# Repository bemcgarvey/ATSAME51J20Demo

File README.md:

# ATSAME51J20Demo
 
## A demonstartion board for the ATSAME51J20 microcontroller.  Includes firmware projects to demonstrate many modules and features.  
  
### There is sample firmware for:
* Basic gpio and interrupts
* Event system
* DMA
* Full speed USB
* SD Card
* USB bootloader and file system boot loader (sd card)
* USB CDC device
* and more

### All firmware is built in MPLabX with MPLab Harmony 3 and the XC32 compiler.  
### Schematic and PCB were made with KiCAD

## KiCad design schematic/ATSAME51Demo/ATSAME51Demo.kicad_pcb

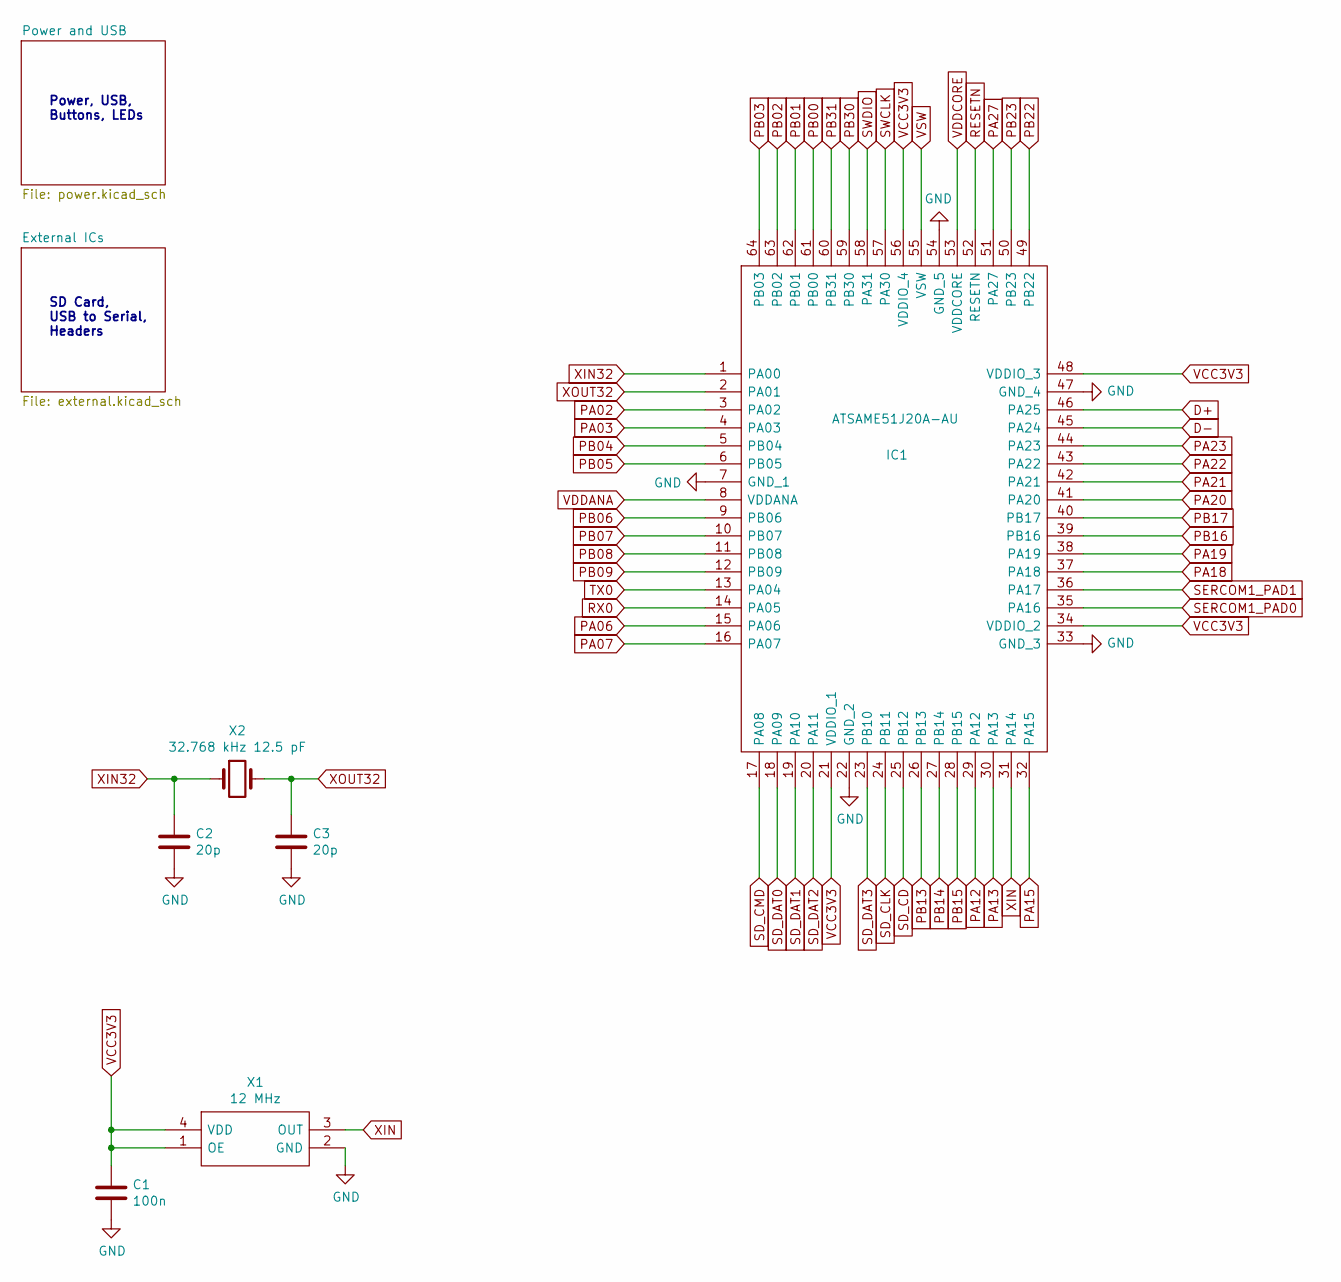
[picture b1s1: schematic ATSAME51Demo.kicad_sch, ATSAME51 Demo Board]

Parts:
C1: 100n; C_0402_1005Metric
C2, C3: 20p; C_0603_1608Metric
IC1: ATSAME51J20A-AU; QFP50P1200X1200X120-64N; Mouser Part Number 556-ATSAME51J20A-AU
X1: 12 MHz; ASTMUPCE3312000MHZLJET; Mouser Part Number 815-UPCE3312LJET
X2: 32.768 kHz 12.5 pF; CM9VT1A

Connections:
D+: IC1.46 (PA25); also elsewhere on the board
D-: IC1.45 (PA24); also elsewhere on the board
GND: C1.2, C2.2, C3.2, IC1.7 (GND_1), IC1.22 (GND_2), IC1.33 (GND_3), IC1.47 (GND_4), IC1.54 (GND_5), X1.2 (GND); also elsewhere on the board
PA02: IC1.3 (PA02); also elsewhere on the board
PA03: IC1.4 (PA03); also elsewhere on the board
PA06: IC1.15 (PA06); also elsewhere on the board
PA07: IC1.16 (PA07); also elsewhere on the board
PA12: IC1.29 (PA12); also elsewhere on the board
PA13: IC1.30 (PA13); also elsewhere on the board
PA15: IC1.32 (PA15); also elsewhere on the board
PA18: IC1.37 (PA18); also elsewhere on the board
PA19: IC1.38 (PA19); also elsewhere on the board
PA20: IC1.41 (PA20); also elsewhere on the board
PA21: IC1.42 (PA21); also elsewhere on the board
PA22: IC1.43 (PA22); also elsewhere on the board
PA23: IC1.44 (PA23); also elsewhere on the board
PA27: IC1.51 (PA27); also elsewhere on the board
PB00: IC1.61 (PB00); also elsewhere on the board
PB01: IC1.62 (PB01); also elsewhere on the board
PB02: IC1.63 (PB02); also elsewhere on the board
PB03: IC1.64 (PB03); also elsewhere on the board
PB04: IC1.5 (PB04); also elsewhere on the board
PB05: IC1.6 (PB05); also elsewhere on the board
PB06: IC1.9 (PB06); also elsewhere on the board
PB07: IC1.10 (PB07); also elsewhere on the board
PB08: IC1.11 (PB08); also elsewhere on the board
PB09: IC1.12 (PB09); also elsewhere on the board
PB13: IC1.26 (PB13); also elsewhere on the board
PB14: IC1.27 (PB14); also elsewhere on the board
PB15: IC1.28 (PB15); also elsewhere on the board
PB16: IC1.39 (PB16); also elsewhere on the board
PB17: IC1.40 (PB17); also elsewhere on the board
PB22: IC1.49 (PB22); also elsewhere on the board
PB23: IC1.50 (PB23); also elsewhere on the board
PB30: IC1.59 (PB30); also elsewhere on the board
PB31: IC1.60 (PB31); also elsewhere on the board
RESETN: IC1.52 (RESETN); also elsewhere on the board
RX0: IC1.14 (PA05); also elsewhere on the board
SD_CD: IC1.25 (PB12); also elsewhere on the board
SD_CLK: IC1.24 (PB11); also elsewhere on the board
SD_CMD: IC1.17 (PA08); also elsewhere on the board
SD_DAT0: IC1.18 (PA09); also elsewhere on the board
SD_DAT1: IC1.19 (PA10); also elsewhere on the board
SD_DAT2: IC1.20 (PA11); also elsewhere on the board
SD_DAT3: IC1.23 (PB10); also elsewhere on the board
SERCOM1_PAD0: IC1.35 (PA16); also elsewhere on the board
SERCOM1_PAD1: IC1.36 (PA17); also elsewhere on the board
SWCLK: IC1.57 (PA30); also elsewhere on the board
SWDIO: IC1.58 (PA31); also elsewhere on the board
TX0: IC1.13 (PA04); also elsewhere on the board
VCC3V3: C1.1, IC1.21 (VDDIO_1), IC1.34 (VDDIO_2), IC1.48 (VDDIO_3), IC1.56 (VDDIO_4), X1.1 (OE), X1.4 (VDD); also elsewhere on the board
VDDANA: IC1.8 (VDDANA); also elsewhere on the board
VDDCORE: IC1.53 (VDDCORE); also elsewhere on the board
VSW: IC1.55 (VSW); also elsewhere on the board
XIN: IC1.31 (PA14), X1.3 (OUT)
XIN32: C2.1, IC1.1 (PA00), X2.1
XOUT32: C3.1, IC1.2 (PA01), X2.2

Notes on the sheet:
Power, USB, Buttons, LEDs
SD Card, USB to Serial, Headers

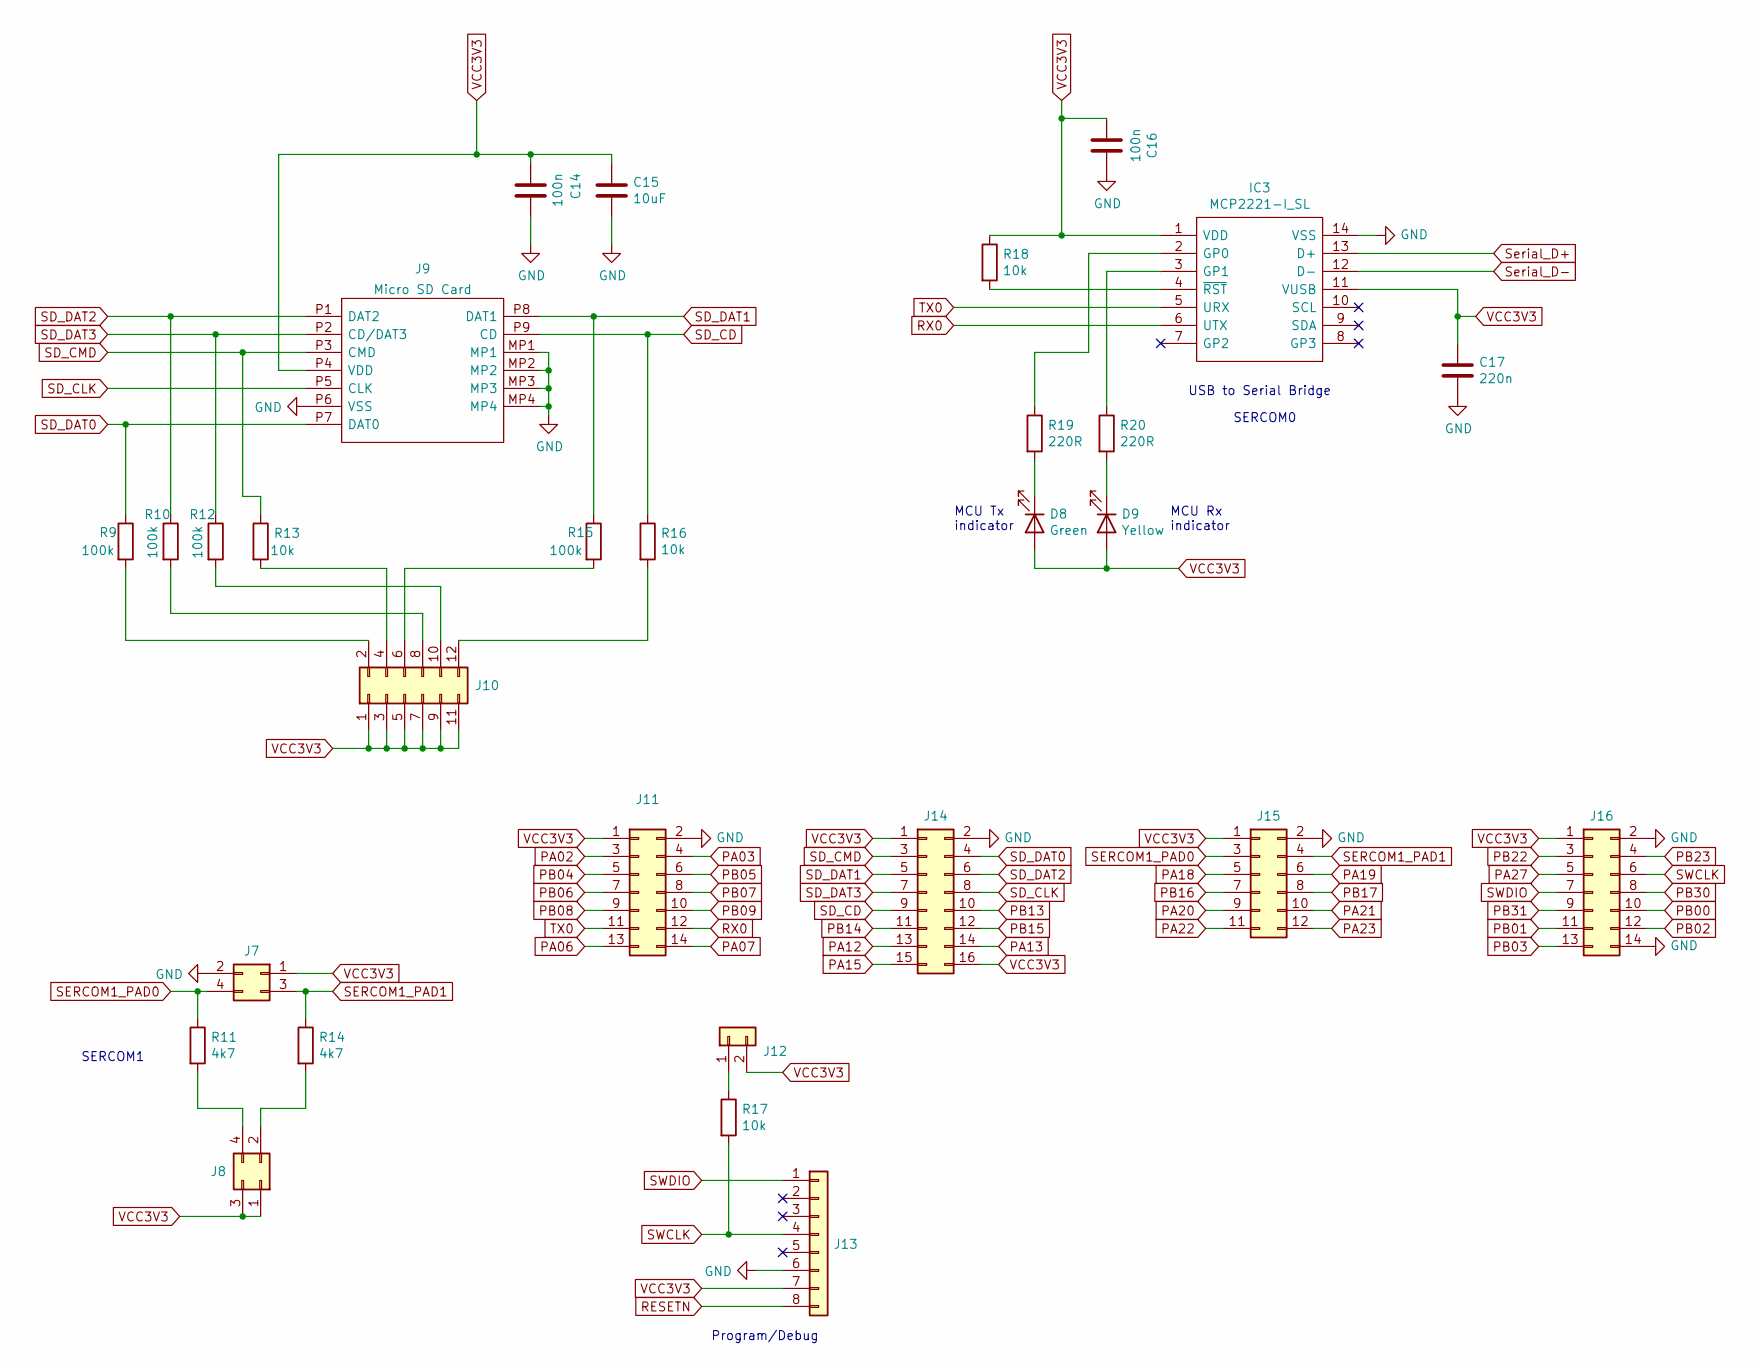
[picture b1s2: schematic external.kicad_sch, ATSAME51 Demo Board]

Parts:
C14, C16: 100n; C_0603_1608Metric
C15: 10uF; C_0603_1608Metric
C17: 220n; C_0603_1608Metric
D8: Green; LED_0603_1608Metric
D9: Yellow; LED_0603_1608Metric
IC3: MCP2221-I_SL; SOIC127P600X175-14N; Mouser Part Number 579-MCP2221-I/SL
J7, J8: Conn_02x02_Odd_Even; PinHeader_2x02_P2.54mm_Vertical
J9: Micro SD Card; MEM20750014001A; Mouser Part Number 640-MEM20750014001A
J10, J15: Conn_02x06_Odd_Even; PinHeader_2x06_P2.54mm_Vertical
J11, J16: Conn_02x07_Odd_Even; PinHeader_2x07_P2.54mm_Vertical
J12: Conn_01x02; PinHeader_1x02_P2.54mm_Vertical
J13: Conn_01x08; PinHeader_1x08_P2.54mm_Horizontal
J14: Conn_02x08_Odd_Even; PinHeader_2x08_P2.54mm_Vertical
R9, R10, R12, R15: 100k; R_0603_1608Metric
R11, R14: 4k7; R_0603_1608Metric
R13, R16, R17, R18: 10k; R_0603_1608Metric
R19, R20: 220R; R_0603_1608Metric

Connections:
GND: C14.1, C15.2, C16.1, C17.2, IC3.14 (VSS), J7.2, J9.MP1, J9.MP2, J9.MP3, J9.MP4, J9.P6 (VSS), J11.2, J13.6, J14.2, J15.2, J16.2, J16.14; also elsewhere on the board
unnamed: D8.1 (K), R19.2
unnamed: D9.1 (K), R20.2
unnamed: IC3.2 (GP0), R19.1
unnamed: IC3.3 (GP1), R20.1
unnamed: IC3.4 (~RST), R18.2
unnamed: J8.2, R14.2
unnamed: J8.4, R11.2
unnamed: J10.2, R9.2
unnamed: J10.4, R13.2
unnamed: J10.6, R15.2
unnamed: J10.8, R10.2
unnamed: J10.10, R12.2
unnamed: J10.12, R16.2
unnamed: J12.1, R17.1
PA02: J11.3; also elsewhere on the board
PA03: J11.4; also elsewhere on the board
PA06: J11.13; also elsewhere on the board
PA07: J11.14; also elsewhere on the board
PA12: J14.13; also elsewhere on the board
PA13: J14.14; also elsewhere on the board
PA15: J14.15; also elsewhere on the board
PA18: J15.5; also elsewhere on the board
PA19: J15.6; also elsewhere on the board
PA20: J15.9; also elsewhere on the board
PA21: J15.10; also elsewhere on the board
PA22: J15.11; also elsewhere on the board
PA23: J15.12; also elsewhere on the board
PA27: J16.5; also elsewhere on the board
PB00: J16.10; also elsewhere on the board
PB01: J16.11; also elsewhere on the board
PB02: J16.12; also elsewhere on the board
PB03: J16.13; also elsewhere on the board
PB04: J11.5; also elsewhere on the board
PB05: J11.6; also elsewhere on the board
PB06: J11.7; also elsewhere on the board
PB07: J11.8; also elsewhere on the board
PB08: J11.9; also elsewhere on the board
PB09: J11.10; also elsewhere on the board
PB13: J14.10; also elsewhere on the board
PB14: J14.11; also elsewhere on the board
PB15: J14.12; also elsewhere on the board
PB16: J15.7; also elsewhere on the board
PB17: J15.8; also elsewhere on the board
PB22: J16.3; also elsewhere on the board
PB23: J16.4; also elsewhere on the board
PB30: J16.8; also elsewhere on the board
PB31: J16.9; also elsewhere on the board
RESETN: J13.8; also elsewhere on the board
RX0: IC3.6 (UTX), J11.12; also elsewhere on the board
SD_CD: J9.P9 (CD), J14.9, R16.1; also elsewhere on the board
SD_CLK: J9.P5 (CLK), J14.8; also elsewhere on the board
SD_CMD: J9.P3 (CMD), J14.3, R13.1; also elsewhere on the board
SD_DAT0: J9.P7 (DAT0), J14.4, R9.1; also elsewhere on the board
SD_DAT1: J9.P8 (DAT1), J14.5, R15.1; also elsewhere on the board
SD_DAT2: J9.P1 (DAT2), J14.6, R10.1; also elsewhere on the board
SD_DAT3: J9.P2 (CD/DAT3), J14.7, R12.1; also elsewhere on the board
SERCOM1_PAD0: J7.4, J15.3, R11.1; also elsewhere on the board
SERCOM1_PAD1: J7.3, J15.4, R14.1; also elsewhere on the board
SWCLK: J13.4, J16.6, R17.2; also elsewhere on the board
SWDIO: J13.1, J16.7; also elsewhere on the board
Serial_D+: IC3.13 (D+); also elsewhere on the board
Serial_D-: IC3.12 (D-); also elsewhere on the board
TX0: IC3.5 (URX), J11.11; also elsewhere on the board
VCC3V3: C14.2, C15.1, C16.2, C17.1, D8.2 (A), D9.2 (A), IC3.1 (VDD), IC3.11 (VUSB), J7.1, J8.1, J8.3, J9.P4 (VDD), J10.1, J10.3, J10.5, J10.7, J10.9, J10.11, J11.1, J12.2, J13.7, J14.1, J14.16, J15.1, J16.1, R18.1; also elsewhere on the board

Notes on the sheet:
MCU Rx indicator
SERCOM1
Program/Debug
SERCOM0
MCU Tx indicator
USB to Serial Bridge

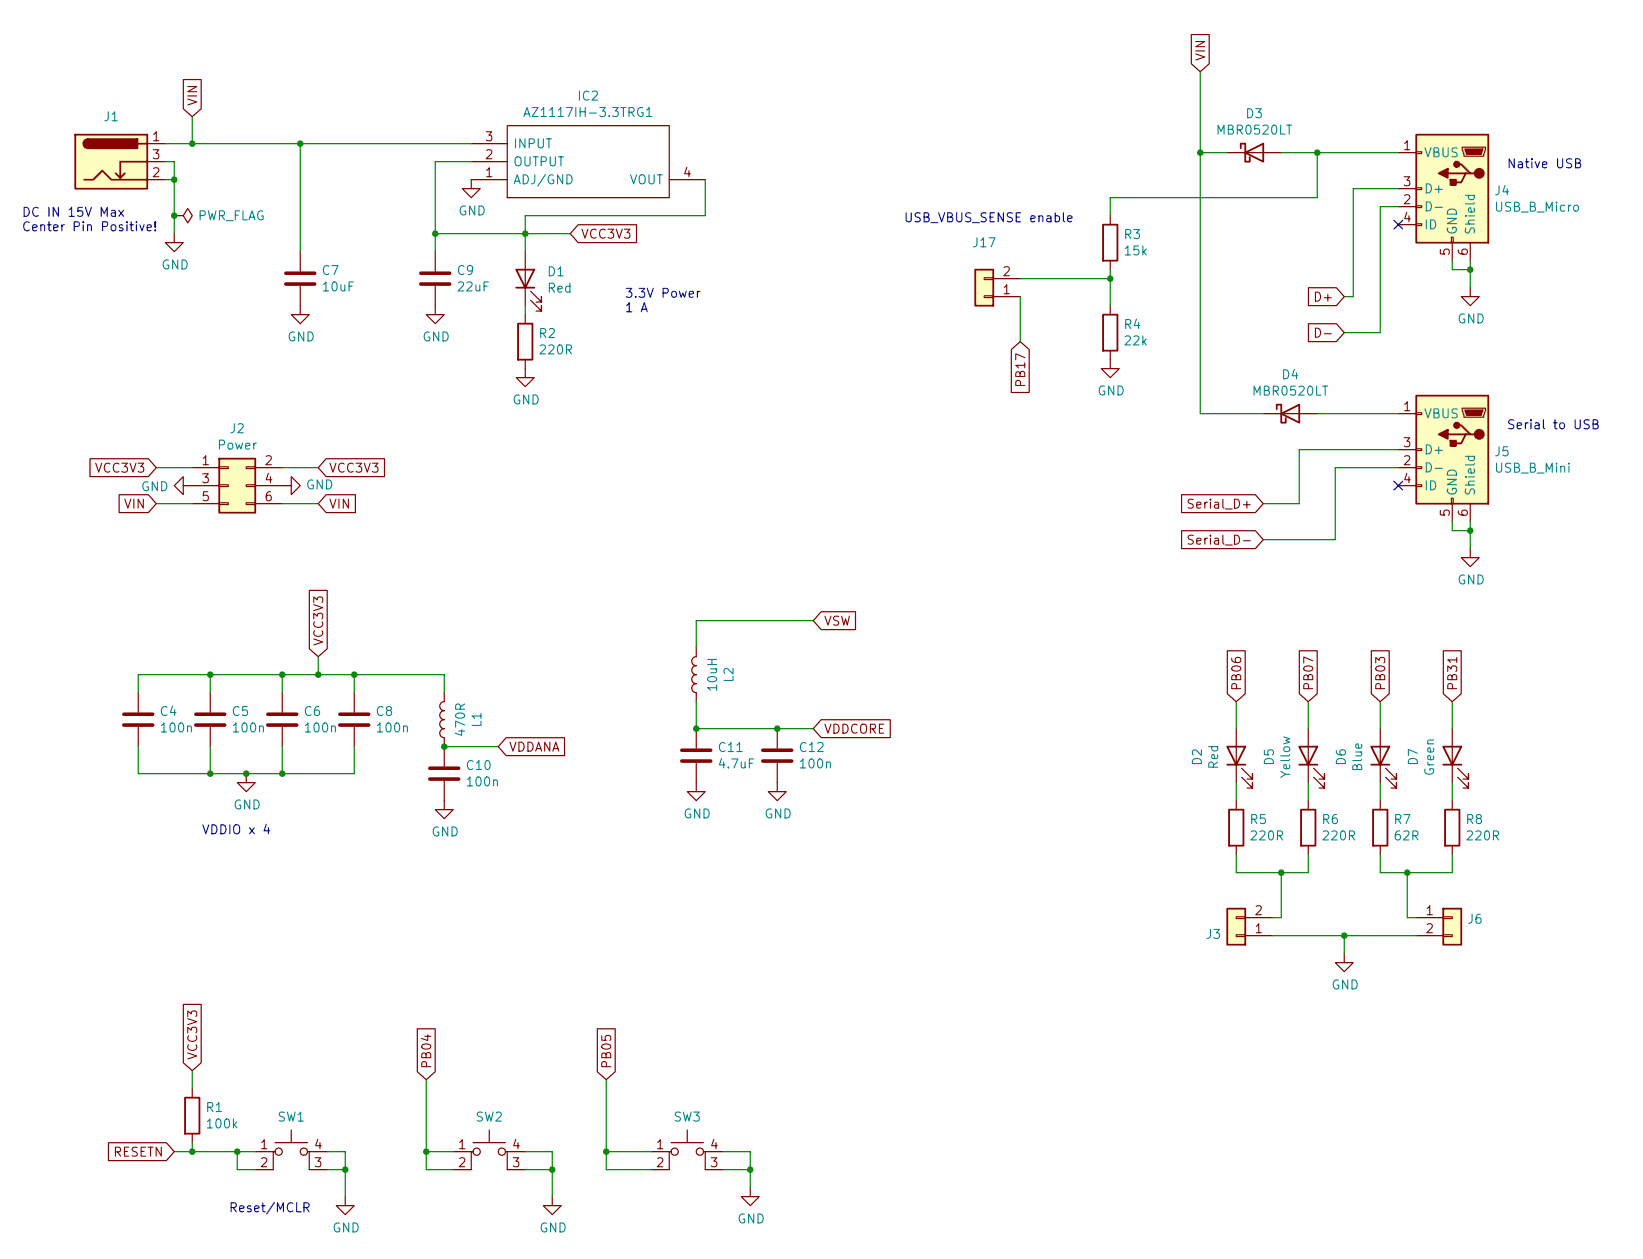
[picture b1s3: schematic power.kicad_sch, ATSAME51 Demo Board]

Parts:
C4, C5, C6, C8, C10, C12: 100n; C_0402_1005Metric
C7: 10uF; C_0805_2012Metric
C9: 22uF; C_0603_1608Metric
C11: 4.7uF; C_0603_1608Metric
D1: Red; LED_0603_1608Metric
D2: Red; LED_0805_2012Metric
D3, D4: MBR0520LT; D_SOD-123
D5: Yellow; LED_0805_2012Metric
D6: Blue; LED_0805_2012Metric
D7: Green; LED_0805_2012Metric
IC2: AZ1117IH-3.3TRG1; SOT230P700X180-4N; Mouser Part Number 621-AZ1117IH-3.3TRG1
J1: Barrel_Jack_Switch; BarrelJack_Wuerth_6941xx301002
J2: Power; PinHeader_2x03_P2.54mm_Vertical
J3, J6, J17: Conn_01x02; PinHeader_1x02_P2.54mm_Vertical
J4: USB_B_Micro; USB_Micro-B_Amphenol_10104110_Horizontal
J5: USB_B_Mini; USB_Mini-B_Wuerth_65100516121_Horizontal
L1: 470R; L_0603_1608Metric
L2: 10uH; L_0603_1608Metric
R1: 100k; R_0603_1608Metric
R2, R5, R6, R8: 220R; R_0603_1608Metric
R3: 15k; R_0603_1608Metric
R4: 22k; R_0603_1608Metric
R7: 62R; R_0603_1608Metric
SW1: SW_MEC_5E; PTS647SK38SMTR2LFS
SW2, SW3: SW_MEC_5E; FSM16JH

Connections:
D+: J4.3 (D+); also elsewhere on the board
D-: J4.2 (D-); also elsewhere on the board
GND: C4.2, C5.2, C6.2, C7.2, C8.2, C9.2, C10.2, C11.2, C12.2, IC2.1 (ADJ/GND), J1.2, J1.3, J2.3, J2.4, J3.1, J4.5 (GND), J4.6 (Shield), J5.5 (GND), J5.6 (Shield), J6.2, R2.2, R4.2, SW1.3 (K), SW1.4 (A), SW2.3 (K), SW2.4 (A), SW3.3 (K), SW3.4 (A); also elsewhere on the board
unnamed: D1.1 (K), R2.1
unnamed: D2.1 (K), R5.1
unnamed: D3.2 (A), J4.1 (VBUS), R3.1
unnamed: D4.2 (A), J5.1 (VBUS)
unnamed: D5.1 (K), R6.1
unnamed: D6.1 (K), R7.1
unnamed: D7.1 (K), R8.1
unnamed: J3.2, R5.2, R6.2
unnamed: J6.1, R7.2, R8.2
unnamed: J17.2, R3.2, R4.1
PB03: D6.2 (A); also elsewhere on the board
PB04: SW2.1, SW2.2; also elsewhere on the board
PB05: SW3.1, SW3.2; also elsewhere on the board
PB06: D2.2 (A); also elsewhere on the board
PB07: D5.2 (A); also elsewhere on the board
PB17: J17.1; also elsewhere on the board
PB31: D7.2 (A); also elsewhere on the board
RESETN: R1.2, SW1.1, SW1.2; also elsewhere on the board
Serial_D+: J5.3 (D+); also elsewhere on the board
Serial_D-: J5.2 (D-); also elsewhere on the board
VCC3V3: C4.1, C5.1, C6.1, C8.1, C9.1, D1.2 (A), IC2.2 (OUTPUT), IC2.4 (VOUT), J2.1, J2.2, L1.2, R1.1; also elsewhere on the board
VDDANA: C10.1, L1.1; also elsewhere on the board
VDDCORE: C11.1, C12.1, L2.1; also elsewhere on the board
VIN: C7.1, D3.1 (K), D4.1 (K), IC2.3 (INPUT), J1.1, J2.5, J2.6
VSW: L2.2; also elsewhere on the board

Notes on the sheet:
Serial to USB
USB_VBUS_SENSE enable
VDDIO x 4
DC IN 15V Max Center Pin Positive!
Native USB
3.3V Power 1 A
Reset/MCLR

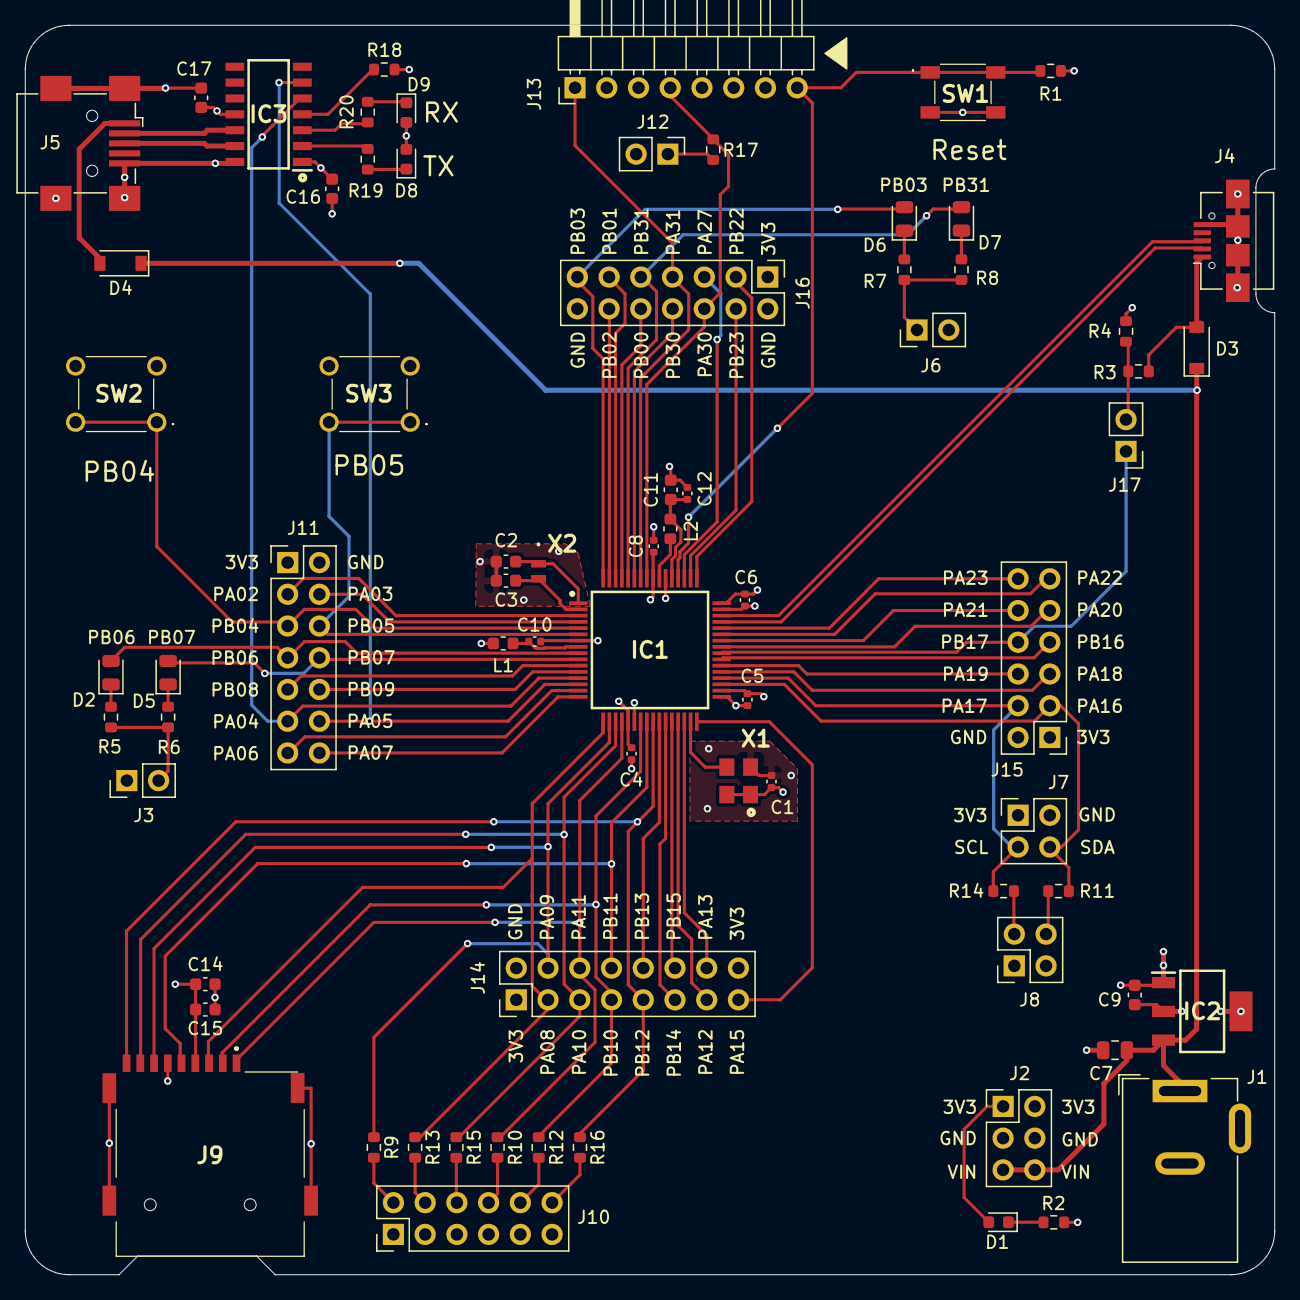
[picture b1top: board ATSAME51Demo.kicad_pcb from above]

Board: 4 copper layers, 100.0 x 100.0 mm, 72 parts (0 on the bottom side), 84 nets.

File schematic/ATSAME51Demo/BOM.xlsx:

Reference | Quantity | Value | Footprint
C1 C4 C5 C6 C8 C10 C12 | 7 | 100n | Capacitor_SMD:C_0402_1005Metric
C11 | 1 | 4.7uF | Capacitor_SMD:C_0603_1608Metric
C15 | 1 | 10uF | Capacitor_SMD:C_0603_1608Metric
C14 C16 | 2 | 100n | Capacitor_SMD:C_0603_1608Metric
C17 | 1 | 220n | Capacitor_SMD:C_0603_1608Metric
C2 C3 | 2 | 20p | Capacitor_SMD:C_0603_1608Metric
C7 | 1 | 10uF | Capacitor_SMD:C_0805_2012Metric
C9 | 1 | 22uF | Capacitor_SMD:C_0603_1608Metric
D1 | 1 | Red | LED_SMD:LED_0603_1608Metric
D2 | 1 | Red | LED_SMD:LED_0805_2012Metric
D3 D4 | 2 | MBR0520LT | Diode_SMD:D_SOD-123
D5 | 1 | Yellow | LED_SMD:LED_0805_2012Metric
D6 | 1 | Blue | LED_SMD:LED_0805_2012Metric
D7 | 1 | Green | LED_SMD:LED_0805_2012Metric
D8 | 1 | Green | LED_SMD:LED_0603_1608Metric
D9 | 1 | Yellow | LED_SMD:LED_0603_1608Metric
IC1 | 1 | ATSAME51J20A-AU | SamacSys_Parts:QFP50P1200X1200X120-64N
IC2 | 1 | AZ1117IH-3.3TRG1 | SamacSys_Parts:SOT230P700X180-4N
IC3 | 1 | MCP2221-I_SL | SamacSys_Parts:SOIC127P600X175-14N
J1 | 1 | Barrel_Jack_Switch | Connector_BarrelJack:BarrelJack_Wuerth_6941xx301002
J10 J15 | 2 | Conn_02x06_Odd_Even | Connector_PinHeader_2.54mm:PinHeader_2x06_P2.54mm_Vertical
J11 J16 | 2 | Conn_02x07_Odd_Even | Connector_PinHeader_2.54mm:PinHeader_2x07_P2.54mm_Vertical
J13 | 1 | Conn_01x08 | Connector_PinHeader_2.54mm:PinHeader_1x08_P2.54mm_Horizontal
J14 | 1 | Conn_02x08_Odd_Even | Connector_PinHeader_2.54mm:PinHeader_2x08_P2.54mm_Vertical
J2 | 1 | Power | Connector_PinHeader_2.54mm:PinHeader_2x03_P2.54mm_Vertical
J3 J6 J12 J17 | 4 | Conn_01x02 | Connector_PinHeader_2.54mm:PinHeader_1x02_P2.54mm_Vertical
J4 | 1 | USB_B_Micro | Connector_USB:USB_Micro-B_Amphenol_10104110_Horizontal
J5 | 1 | USB_B_Mini | Connector_USB:USB_Mini-B_Wuerth_65100516121_Horizontal
J7 J8 | 2 | Conn_02x02_Odd_Even | Connector_PinHeader_2.54mm:PinHeader_2x02_P2.54mm_Vertical
J9 | 1 | Micro SD Card | SamacSys_Parts:MEM20750014001A
L1 | 1 | 470R | Inductor_SMD:L_0603_1608Metric
L2 | 1 | 10uH | Inductor_SMD:L_0603_1608Metric
R1 R9 R10 R12 R15 | 5 | 100k | Resistor_SMD:R_0603_1608Metric
R11 R14 | 2 | 4k7 | Resistor_SMD:R_0603_1608Metric
R13 R16 R17 R18 | 4 | 10k | Resistor_SMD:R_0603_1608Metric
R2 R5 R6 R8 R19 R20 | 6 | 220R | Resistor_SMD:R_0603_1608Metric
R3 | 1 | 15k | Resistor_SMD:R_0603_1608Metric
R4 | 1 | 22k | Resistor_SMD:R_0603_1608Metric
R7 | 1 | 62R | Resistor_SMD:R_0603_1608Metric
SW1 | 1 | SW_MEC_5E | SamacSys_Parts:PTS647SK38SMTR2LFS
SW2 SW3 | 2 | SW_MEC_5E | SamacSys_Parts:FSM16JH
X1 | 1 | 12 MHz | SamacSys_Parts:ASTMUPCE3312000MHZLJET
X2 | 1 | 32.768 kHz 12.5 pF | SamacSys_Parts:CM9VT1A

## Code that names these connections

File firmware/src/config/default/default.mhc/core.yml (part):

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    - type: Values
      children:
      - type: Dynamic
        attributes: {id: core, value: PA00}
  - type: String
    attributes: {id: PORT_GROUP_0_PAD_1}
    children:
    - type: Values
      children:
      - type: Dynamic
        attributes: {id: core, value: PA01}
  - type: String
    attributes: {id: PORT_GROUP_0_PAD_14}
    children:
    - type: Values
      children:
      - type: Dynamic
        attributes: {id: core, value: PA14}
  - type: String
    attributes: {id: PORT_GROUP_0_PAD_4}
    children:
    - type: Values
      children:
      - type: Dynamic
        attributes: {id: core, value: PA04}
  - type: String
    attributes: {id: PORT_GROUP_0_PAD_5}
    children:
    - type: Values
      children:
      - type: Dynamic
        attributes: {id: core, value: PA05}
  - type: String
    attributes: {id: PORT_GROUP_0_PINCFG0}
    children:
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    - type: Values
      children:
      - type: Dynamic
        attributes: {id: core, value: PB03}
  - type: String
    attributes: {id: PORT_GROUP_1_PAD_31}
    children:
    - type: Values
      children:
      - type: Dynamic
        attributes: {id: core, value: PB31}
  - type: String
    attributes: {id: PORT_GROUP_1_PAD_4}
    children:
    - type: Values
      children:
      - type: Dynamic
        attributes: {id: core, value: PB04}
  - type: String
    attributes: {id: PORT_GROUP_1_PAD_5}
    children:
    - type: Values
      children:
      - type: Dynamic
        attributes: {id: core, value: PB05}
  - type: String
    attributes: {id: PORT_GROUP_1_PAD_6}
    children:
    - type: Values
      children:
      - type: Dynamic
        attributes: {id: core, value: PB06}
  - type: String
    attributes: {id: PORT_GROUP_1_PAD_7}
    children:
    - type: Values
      children:
      - type: Dynamic
        attributes: {id: core, value: PB07}
  - type: String
    attributes: {id: PORT_GROUP_1_PINCFG3}
    children:
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
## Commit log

2021-10-23 Initial commit with KiCad project
2021-10-25 Schematic first draft
    Still needs footprints
2021-10-25 Footprints assigned
2021-10-25 PCB design rules set
    4 Layer JLCPCB settings
2021-10-25 Removed USB detect
2021-10-26 First draft PCB layout
    Still needs silkscreen cleanup
2021-10-26 Front silkscreen done
2021-10-26 Moved SD card back from edge
    Rearranged some connections to improve routing
2021-11-10 Adjusted sd card footprint
2021-11-10 Fixed micro usb footprint
2021-11-14 Added USB_VBUS_SENSE
    And other minor improvements
2021-11-16 Changed leds to 0805
2021-11-19 Production gerbers
2021-11-26 Added ATSAME51 errata
2021-12-16 Initial Harmony project
2021-12-16 Event system working
2021-12-17 Simplified main
2021-12-18 Added MSD demo
    Restructured firmware directory
2021-12-18 SD card working with MSD
2021-12-18 Changed sd to high speed
2021-12-18 LCD and I2C working
2021-12-22 MSD multiple LUNS working
2021-12-24 Quadrature decoder working
2021-12-24 Added USB bootloader
2021-12-24 RTC working (and switching regulator)
2021-12-24 Added file system bootloader
2021-12-29 Added DMA demo
2021-12-29 Initial CDC demo
2021-12-29 CDC demo working
2021-12-29 Switched CDC demo to RTOS
2021-12-29 Added large transfer
2021-12-29 Added MSD to CDC demo to create composite device
2021-12-29 Changed msd manufacturer string
2021-12-30 ADC working
2021-12-30 Setup crystalless usb clock for MSD demo
2022-01-19 Converted to KiCad 6
